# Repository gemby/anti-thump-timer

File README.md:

# Anti-thump timer
Timer for protecting headphones from power-on thump. It is projected for use in tube headphone amplifiers, since they are prone to thumps, or more precisely voltage spikes during power on. It is powered from 6.3V AC voltage for tube heater.

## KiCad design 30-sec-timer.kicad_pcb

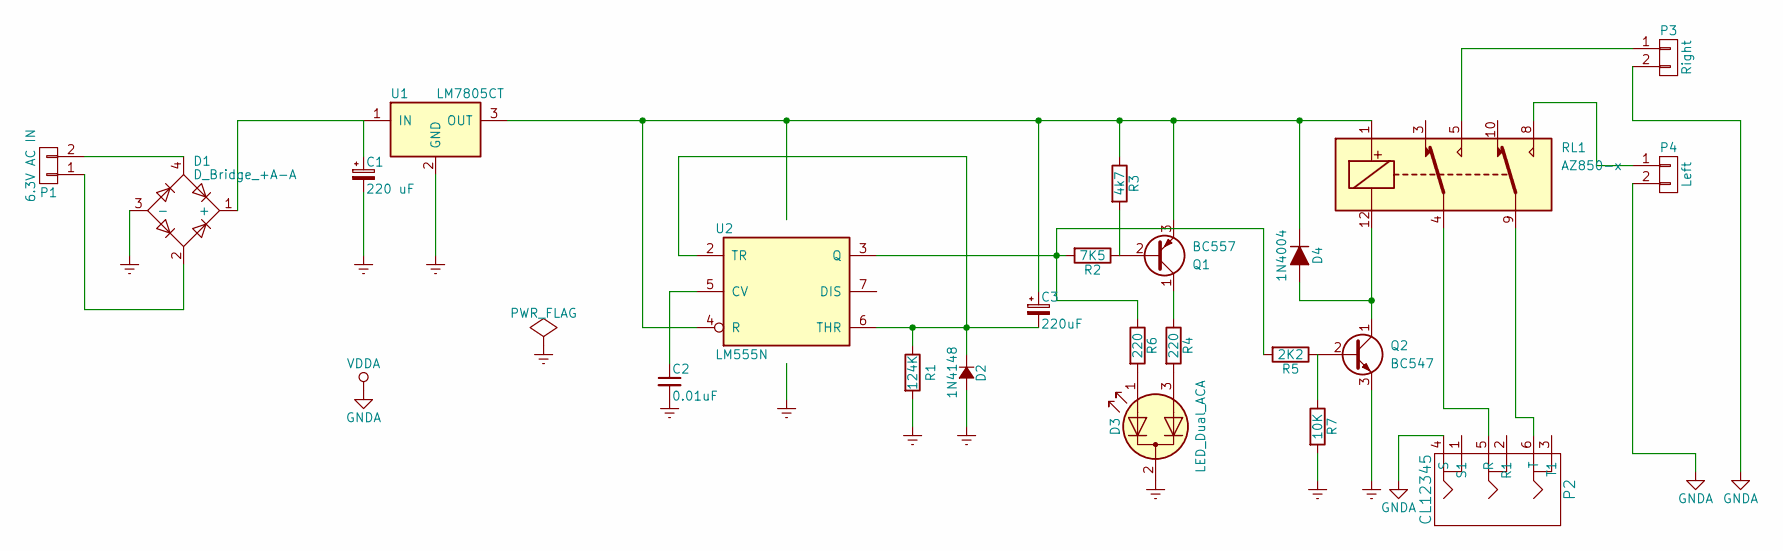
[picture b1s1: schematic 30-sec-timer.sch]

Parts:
C1: 220 uF; CP_Radial_D6.3mm_P2.50mm
C2: 0.01uF; C_Disc_D7.5mm_W4.4mm_P5.00mm
C3: 220uF; CP_Radial_D6.3mm_P2.50mm
D1: D_Bridge_+A-A; Diode_Bridge_Round_D8.9mm
D2: 1N4148; D_DO-35_SOD27_P7.62mm_Horizontal
D3: LED_Dual_ACA; LED_D3.0mm-3
D4: 1N4004; D_DO-35_SOD27_P7.62mm_Horizontal
P1: 6.3V AC IN; JST_XH_B02B-XH-A_02x2.50mm_Straight
P2: CL12345
P3: Right; JST_XH_B02B-XH-A_02x2.50mm_Straight
P4: Left; JST_XH_B02B-XH-A_02x2.50mm_Straight
Q1: BC557; TO-92_Inline_Narrow_Oval
Q2: BC547; TO-92_Inline_Narrow_Oval
R1: 124K; R_Axial_DIN0207_L6.3mm_D2.5mm_P7.62mm_Horizontal
R2: 7K5; R_Axial_DIN0207_L6.3mm_D2.5mm_P7.62mm_Horizontal
R3: 4k7; R_Axial_DIN0207_L6.3mm_D2.5mm_P7.62mm_Horizontal
R4, R6: 220; R_Axial_DIN0207_L6.3mm_D2.5mm_P7.62mm_Horizontal
R5: 2K2; R_Axial_DIN0207_L6.3mm_D2.5mm_P7.62mm_Horizontal
R7: 10K; R_Axial_DIN0207_L6.3mm_D2.5mm_P7.62mm_Horizontal
RL1: AZ850-x; Relay_DPDT_AXICOM_V23079_Pitch5.08mm
U1: LM7805CT; TO-220-3_Horizontal
U2: LM555N; DIP-8_W7.62mm_LongPads

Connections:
Earth: C1.2, C2.2, D1.3 (-), D2.2 (A), D3.2 (K), Q2.3 (E), R1.2, R7.2, U1.2 (GND), U2.1 (GND)
GNDA: P2.4 (S), P3.2, P4.2
unnamed: C1.1, D1.1 (+), U1.1 (IN)
unnamed: C2.1, U2.5 (CV)
unnamed: C3.2, D2.1 (K), R1.1, U2.2 (TR), U2.6 (THR)
unnamed: D1.2, P1.1
unnamed: D1.4, P1.2
unnamed: D3.1 (A1), R6.2
unnamed: D3.3 (A2), R4.2
unnamed: D4.2 (A), Q2.1 (C), RL1.12
unnamed: P2.5 (R), RL1.4
unnamed: P2.6 (T), RL1.9
unnamed: P3.1, RL1.5
unnamed: P4.1, RL1.8
unnamed: Q1.1 (C), R4.1
unnamed: Q1.2 (B), R2.1, R3.2
unnamed: Q2.2 (B), R5.1, R7.1
unnamed: R2.2, R5.2, R6.1, U2.3 (Q)
VCC: C3.1, D4.1 (K), Q1.3 (E), R3.1, RL1.1, U1.3 (OUT), U2.4 (R), U2.8 (VCC)

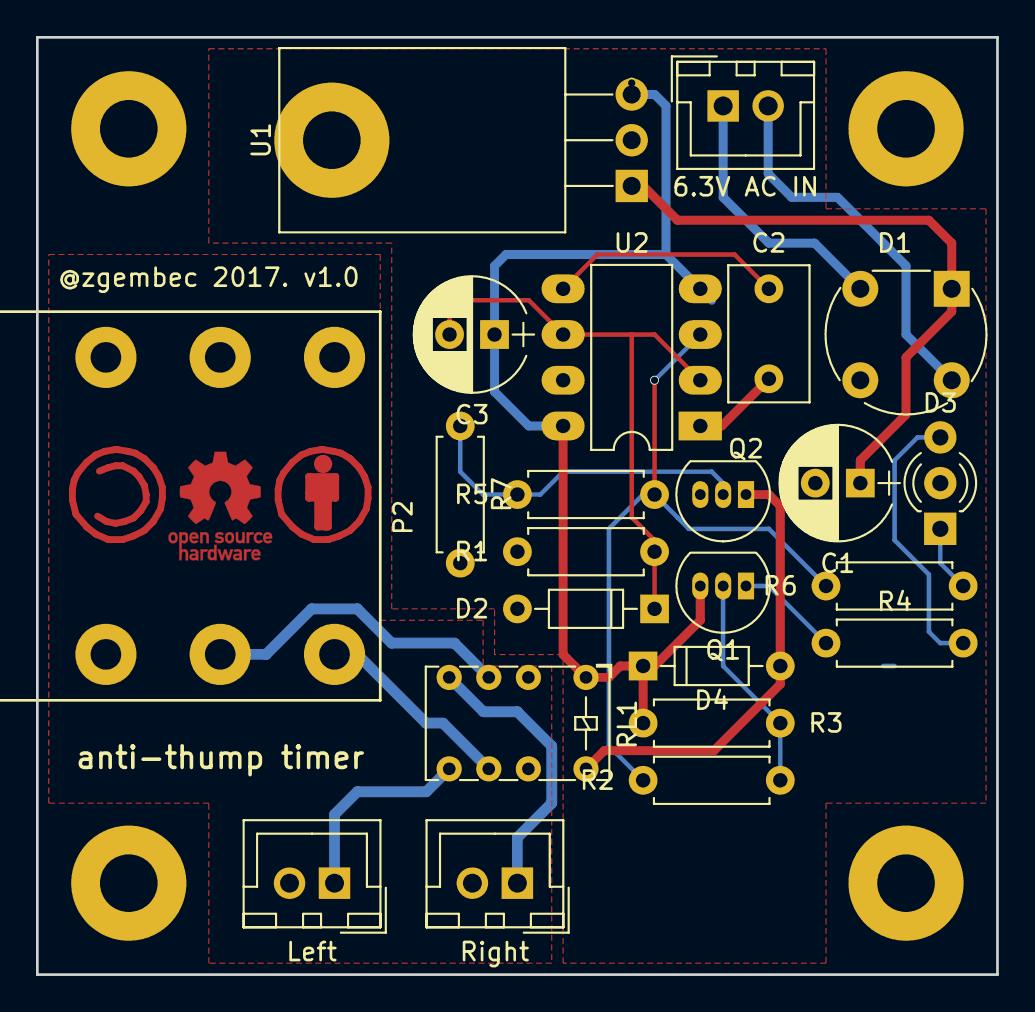
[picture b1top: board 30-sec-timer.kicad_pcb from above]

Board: 2 copper layers, 53.3 x 52.1 mm, 23 parts (0 on the bottom side), 19 nets.

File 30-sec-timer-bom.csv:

"Id";"Designator";"Package";"Quantity";"Designation";"Supplier and ref";
1;"P2";"CL12345";1;"CL12345";;;
2;"REF**,REF**,REF**,REF**";"MountingHole_3.2mm_M3_Pad";4;"M3_Pad";;;
3;"U2";"DIP-8_W7.62mm_LongPads";1;"LM555N";;;
4;"U1";"TO-220-3_Horizontal";1;"LM7805CT";;;
5;"P1";"JST_XH_B02B-XH-A_02x2.50mm_Straight";1;"6.3V AC IN";;;
6;"R1";"R_Axial_DIN0207_L6.3mm_D2.5mm_P7.62mm_Horizontal";1;"124K";;;
7;"R2";"R_Axial_DIN0207_L6.3mm_D2.5mm_P7.62mm_Horizontal";1;"7K5";;;
8;"R3";"R_Axial_DIN0207_L6.3mm_D2.5mm_P7.62mm_Horizontal";1;"4k7";;;
9;"R4,R6";"R_Axial_DIN0207_L6.3mm_D2.5mm_P7.62mm_Horizontal";2;"220";;;
10;"R5";"R_Axial_DIN0207_L6.3mm_D2.5mm_P7.62mm_Horizontal";1;"2K2";;;
11;"C2";"C_Disc_D7.5mm_W4.4mm_P5.00mm";1;"0.01uF";;;
12;"D2";"D_DO-35_SOD27_P7.62mm_Horizontal";1;"1N4148";;;
13;"D3";"LED_D3.0mm-3";1;"LED_Dual_ACA";;;
14;"D4";"D_DO-35_SOD27_P7.62mm_Horizontal";1;"1N4004";;;
15;"RL1";"Relay_DPDT_AXICOM_V23079_Pitch5.08mm";1;"AZ850-x";;;
16;"P3";"JST_XH_B02B-XH-A_02x2.50mm_Straight";1;"Right";;;
17;"P4";"JST_XH_B02B-XH-A_02x2.50mm_Straight";1;"Left";;;
18;"D1";"Diode_Bridge_Round_D8.9mm";1;"D_Bridge_+A-A";;;
19;"C1";"CP_Radial_D6.3mm_P2.50mm";1;"220 uF";;;
20;"C3";"CP_Radial_D6.3mm_P2.50mm";1;"220uF";;;
21;"Q1";"TO-92_Inline_Narrow_Oval";1;"BC557";;;
22;"Q2";"TO-92_Inline_Narrow_Oval";1;"BC547";;;
23;"R7";"R_Axial_DIN0207_L6.3mm_D2.5mm_P7.62mm_Horizontal";1;"10K";;;
24;"REF***";"OSHW-Logo_5.7x6mm_Copper";1;"OSHW-Logo_5.7x6mm_Copper";;;
25;"REF**";"Symbol_CC-ShareAlike_CopperTop_Small";1;"Symbol_CC-ShareAlike_CopperTop_Small";;;
26;"REF**";"Symbol_CC-Attribution_CopperTop_Small";1;"Symbol_CC-Attribution_CopperTop_Small";;;

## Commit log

2017-11-11 kicad project commit
2017-11-11 Readme fix
2017-11-11 7805 mounting hole fix
2017-11-11 relay driveing fix, resistor values fix, added two resistors for led, led brightness fix
2017-11-11 BOM fix
2017-11-12 resistor placement fix
